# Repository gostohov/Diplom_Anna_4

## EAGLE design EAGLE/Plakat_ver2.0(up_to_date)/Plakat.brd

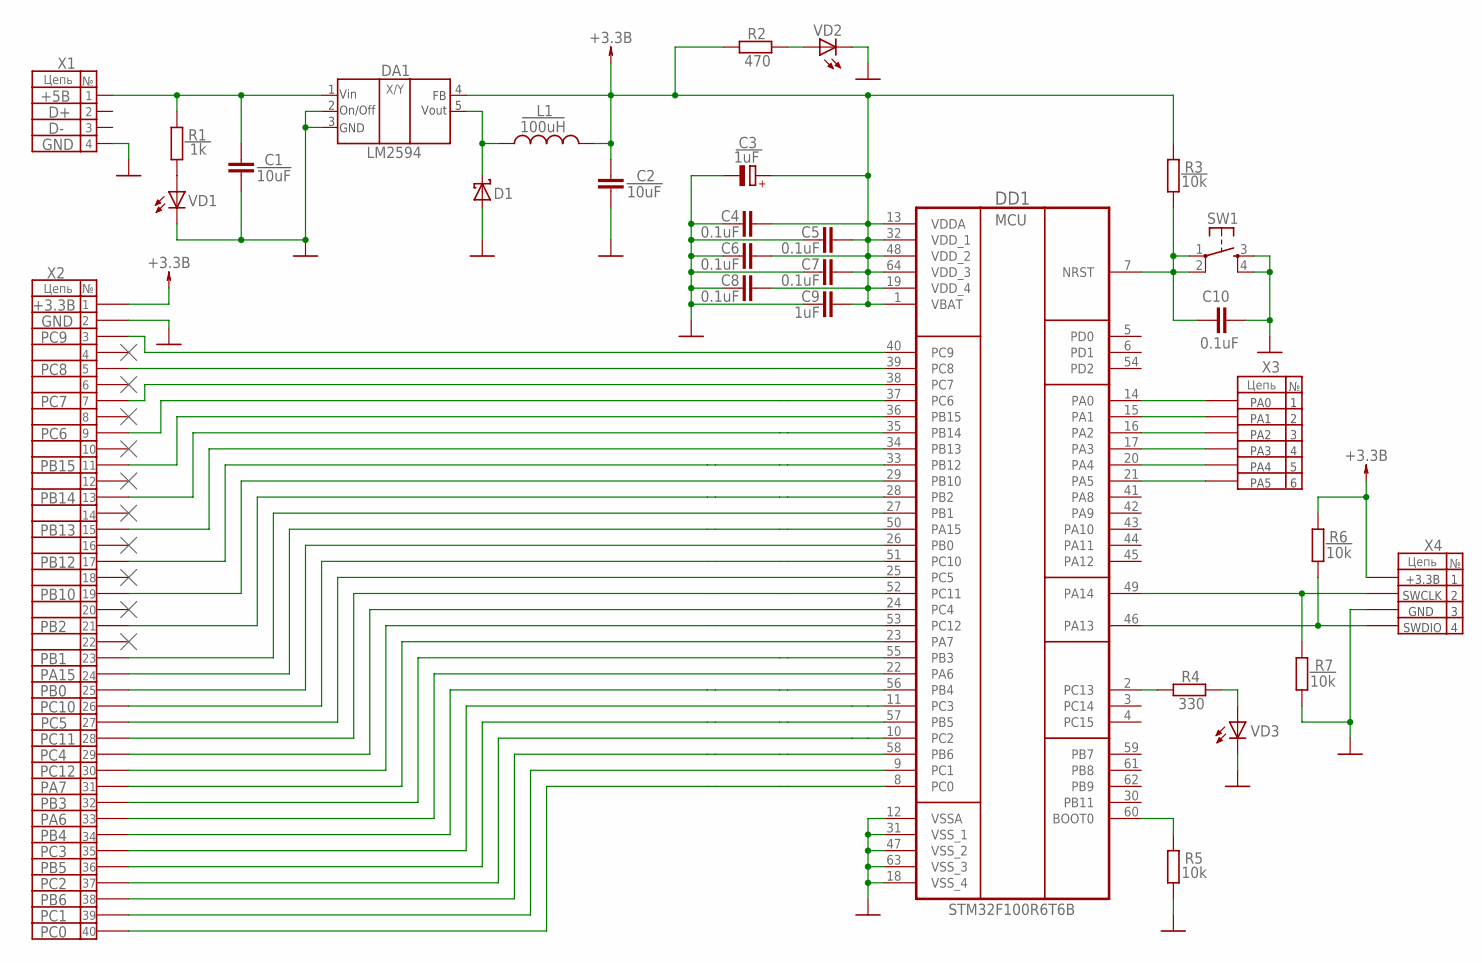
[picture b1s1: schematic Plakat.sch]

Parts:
C1, C2: 10uF; C0805
C3: 1uF; TYPE_A_TECAP
C4, C5, C6, C7, C8, C10: 0.1uF; C0805
C9: 1uF; C0805
D1: 1N5819-T; DO41-7.6
DA1: LM2594; LM2495
DD1: STM32F100R6T6B; QFP50P1200X1200X160-64N
L1: 100uH; 101KL
R1: 1k; R0805
R2: 470; R0805
R3, R5, R6, R7: 10k; R0805
R4: 330; R0805
SW1: DTSM-6
VD1, VD2, VD3: LED_E; LED_1206
X1: USB-MICROB
X2: PINHD-2X20; 2X20
X3: PINHD-1X6; 1X06
X4: PINHD-1X4; 1X04

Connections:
5V: C1.1, DA1.V(IN), R1.2, X1.VBUS
GND: C1.2, C2.2, C3.-, C4.1, C5.1, C6.1, C7.1, C8.1, C9.1, C10.2, D1.A, DA1.GND, DA1.ON/OFF, DD1.12 (VSSA), DD1.18 (VSS_4), DD1.31 (VSS_1), DD1.47 (VSS_2), DD1.63 (VSS_3), R5.1, R7.1, SW1.3, SW1.4, VD1.C, VD2.C, VD3.C, X1.GND, X1.MT1 (GND), X1.MT2 (GND), X2.2, X4.3
unnamed: DD1.60 (BOOT0), R5.2
unnamed: D1.C, DA1.OUT, L1.2
unnamed: DD1.14 (PA0), X3.1
unnamed: R1.1, VD1.A
unnamed: R4.2, VD3.A
unnamed: DD1.15 (PA1), X3.2
unnamed: DD1.2 (PC13), R4.1
unnamed: DD1.16 (PA2), X3.3
unnamed: DD1.17 (PA3), X3.4
unnamed: DD1.20 (PA4), X3.5
unnamed: DD1.21 (PA5), X3.6
unnamed: R2.2, VD2.A
unnamed: DD1.53 (PC12), X2.30
unnamed: C10.1, DD1.7 (NRST), R3.1, SW1.1, SW1.2
unnamed: DD1.40 (PC9), X2.3
unnamed: DD1.39 (PC8), X2.5
unnamed: DD1.38 (PC7), X2.7
unnamed: DD1.37 (PC6), X2.9
unnamed: DD1.36 (PB15), X2.11
unnamed: DD1.35 (PB14), X2.13
unnamed: DD1.34 (PB13), X2.15
unnamed: DD1.33 (PB12), X2.17
unnamed: DD1.29 (PB10), X2.19
unnamed: DD1.28 (PB2), X2.21
unnamed: DD1.27 (PB1), X2.23
unnamed: DD1.50 (PA15), X2.24
unnamed: DD1.26 (PB0), X2.25
unnamed: DD1.51 (PC10), X2.26
unnamed: DD1.25 (PC5), X2.27
unnamed: DD1.52 (PC11), X2.28
unnamed: DD1.24 (PC4), X2.29
unnamed: DD1.23 (PA7), X2.31
unnamed: DD1.55 (PB3), X2.32
unnamed: DD1.22 (PA6), X2.33
unnamed: DD1.56 (PB4), X2.34
unnamed: DD1.11 (PC3), X2.35
unnamed: DD1.57 (PB5), X2.36
unnamed: DD1.10 (PC2), X2.37
unnamed: DD1.58 (PB6), X2.38
unnamed: DD1.9 (PC1), X2.39
unnamed: DD1.8 (PC0), X2.40
SWCLK: DD1.49 (PA14), R7.2, X4.2
SWDIO: DD1.46 (PA13), R6.1, X4.4
VCC: C2.1, C3.+, C4.2, C5.2, C6.2, C7.2, C8.2, C9.2, DA1.FB, DD1.1 (VBAT), DD1.13 (VDDA), DD1.19 (VDD_4), DD1.32 (VDD_1), DD1.48 (VDD_2), DD1.64 (VDD_3), L1.1, R2.1, R3.2, R6.2, X2.1, X4.1

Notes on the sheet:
Цепь
+5B
GND
Vin
On/Off
Vout
+3.3В
SWDIO
SWCLK
PA0
PA1
PA2
PA3
PA4
PA5
MCU
PC9
PC8
PC7
PC6
PB15
PB14
PB13
PB12
PB10
PB2
PB1
PA15
PB0
PC10
PC5
PC11
PC4
PC12
PA7
PB3
PA6
PB4
PC3
PB5

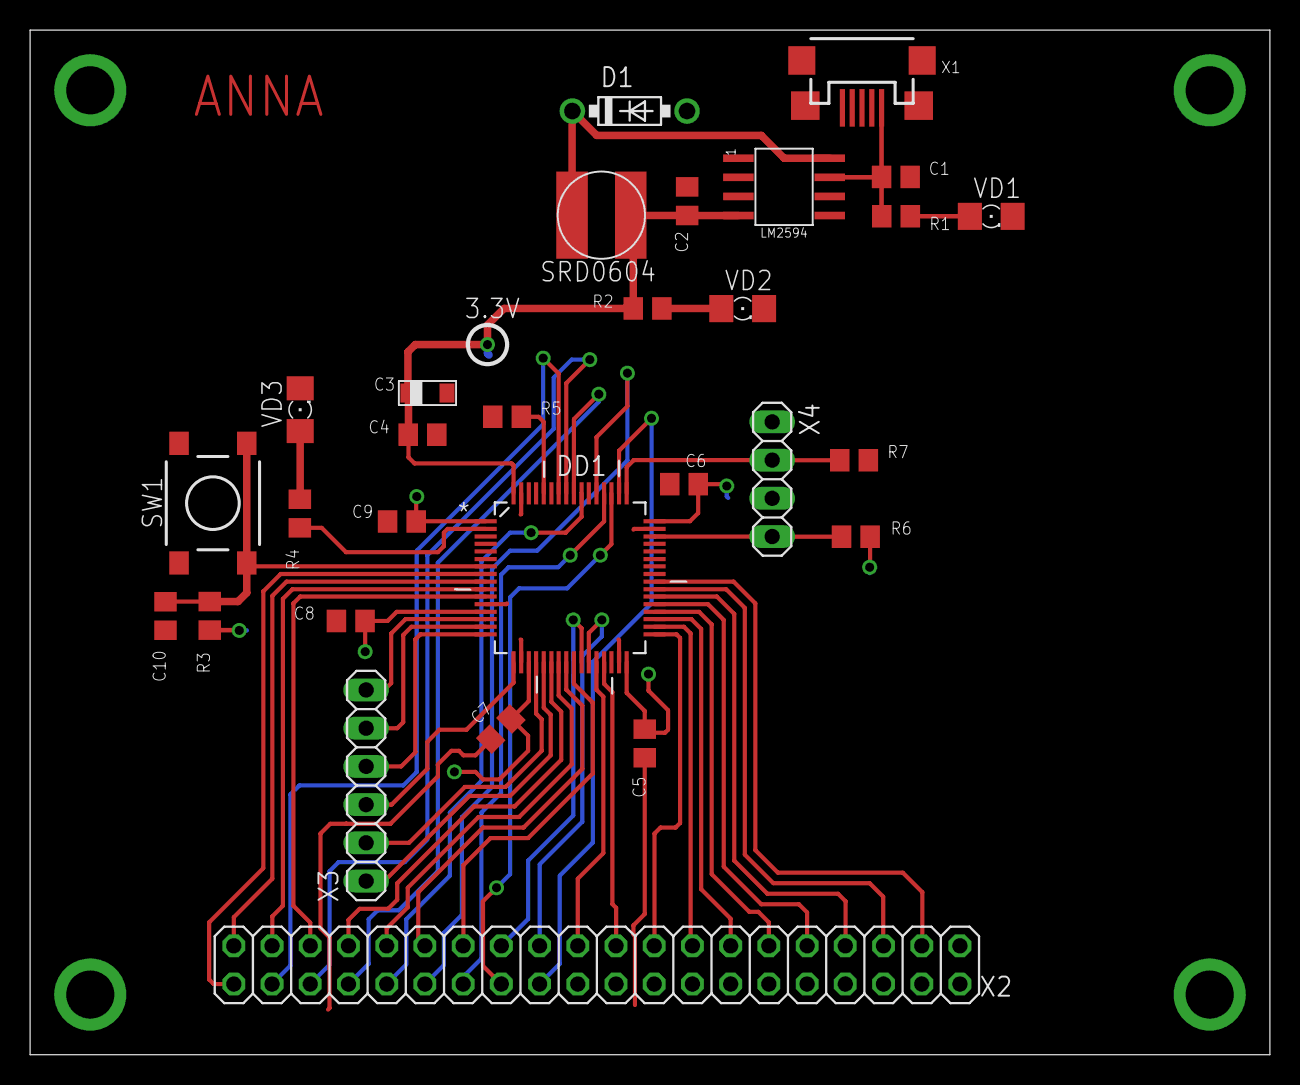
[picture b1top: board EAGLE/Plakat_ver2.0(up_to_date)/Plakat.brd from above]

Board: 2 copper layers, 82.4 x 68.1 mm, 29 parts (0 on the bottom side), 46 nets.

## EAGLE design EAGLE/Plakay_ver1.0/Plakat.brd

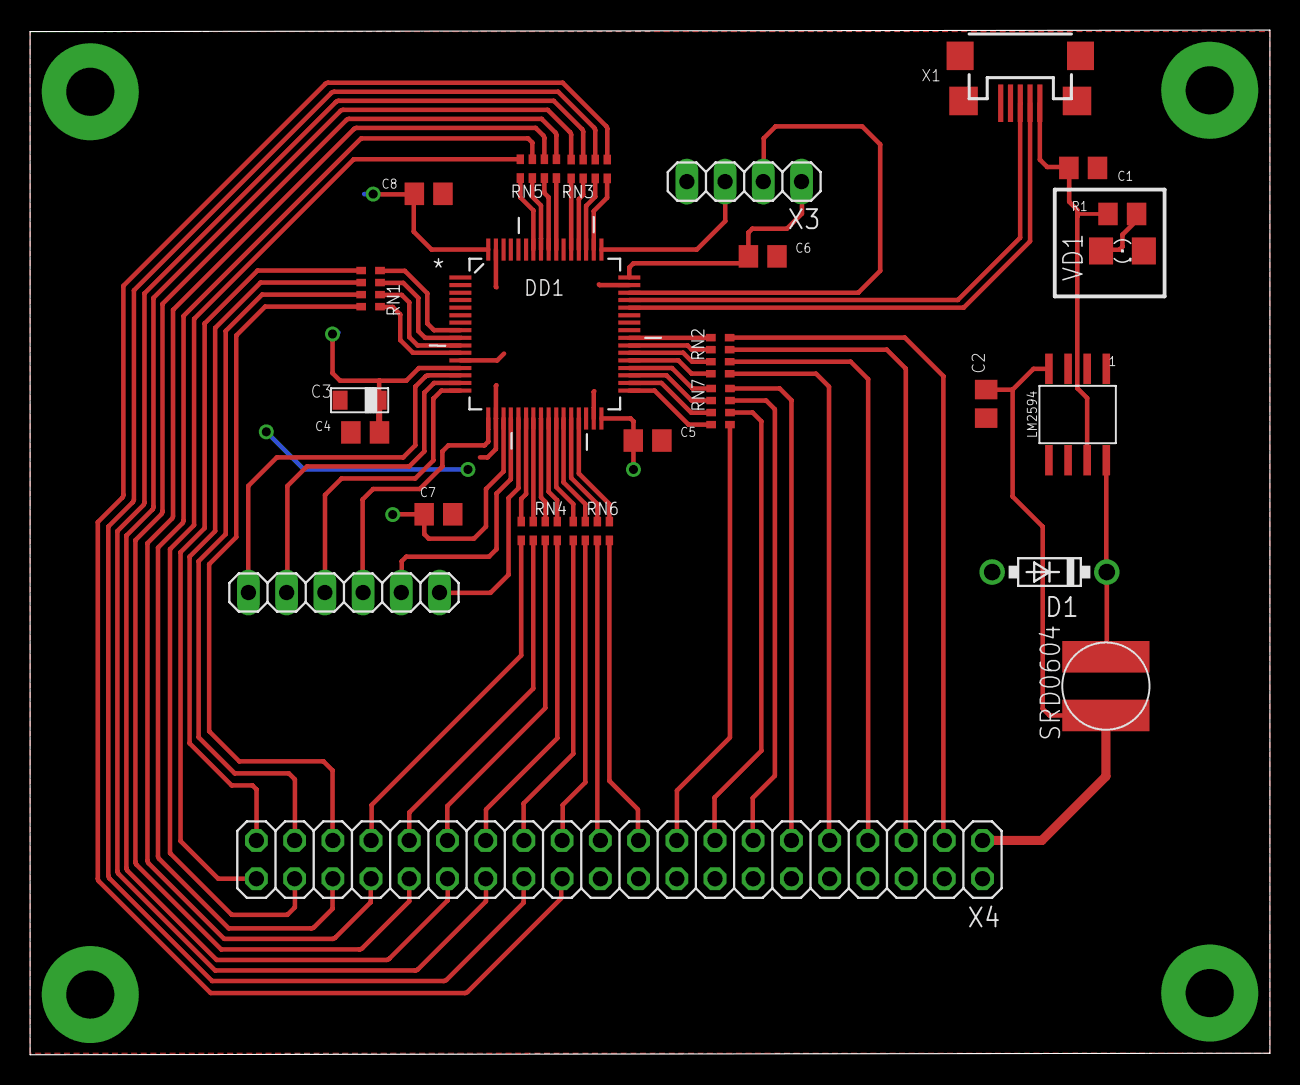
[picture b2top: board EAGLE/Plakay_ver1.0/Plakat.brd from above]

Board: 2 copper layers, 82.4 x 68.1 mm, 25 parts (0 on the bottom side), 71 nets.

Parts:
C1, C2: 10uF; C0805
C3: 1uF; TYPE_A_TECAP
C4, C5, C6, C7, C8: 100nF; C0805
D1: 1N5819-T; DO41-7.6
DA1: LM2594; LM2495
DD1: STM32F100R6T6B; QFP50P1200X1200X160-64N
L1: 100uH; 101KL
R1: 470; R0805
RN1, RN2, RN3, RN4, RN5, RN6, RN7: 100; 0603-ARC
VD1: LED_1206
X1: USB-MICROB
X2: 1X06
X3: 1X04
X4: 2X20

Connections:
DM: DD1.44, X1.D-
DP: DD1.45, X1.D+
GND: C1.2, C2.2, C3.-, C4.2, C5.2, C6.2, C7.2, C8.2, D1.A, DA1.GND, DA1.ON/OFF, DD1.12, DD1.18, DD1.31, DD1.47, DD1.63, VD1.C, X1.GND, X1.MT1, X1.MT2, X3.4, X4.2
unnamed: C1.1, DA1.V(IN), R1.2, X1.VBUS
unnamed: D1.C, DA1.OUT, L1.2
unnamed: DD1.14, X2.1
unnamed: R1.1, VD1.A
unnamed: DD1.8, RN1.4
unnamed: DD1.15, X2.2
unnamed: DD1.9, RN1.3
unnamed: DD1.16, X2.3
unnamed: DD1.17, X2.4
unnamed: DD1.20, X2.5
unnamed: DD1.21, X2.6
unnamed: DD1.10, RN1.2
unnamed: DD1.11, RN1.1
unnamed: DD1.24, RN4.2
unnamed: DD1.25, RN4.1
unnamed: DD1.37, RN2.4
unnamed: DD1.38, RN2.3
unnamed: DD1.39, RN2.2
unnamed: DD1.40, RN2.1
unnamed: DD1.51, RN3.3
unnamed: DD1.50, RN3.4
unnamed: DD1.22, RN4.4
unnamed: DD1.23, RN4.3
unnamed: DD1.26, RN6.4
unnamed: DD1.27, RN6.3
unnamed: DD1.55, RN5.4
unnamed: DD1.56, RN5.3
unnamed: DD1.57, RN5.2
unnamed: DD1.58, RN5.1
unnamed: DD1.28, RN6.2
unnamed: DD1.29, RN6.1
unnamed: DD1.33, RN7.4
unnamed: DD1.34, RN7.3
unnamed: DD1.35, RN7.2
unnamed: DD1.36, RN7.1
unnamed: RN2.8, X4.3
unnamed: RN2.7, X4.5
unnamed: RN2.6, X4.7
unnamed: RN2.5, X4.9
unnamed: RN7.8, X4.11
unnamed: RN7.7, X4.13
unnamed: RN7.6, X4.15
unnamed: RN7.5, X4.17
unnamed: RN6.8, X4.19
unnamed: RN6.7, X4.21
unnamed: RN6.6, X4.23
unnamed: RN6.5, X4.25
unnamed: RN4.8, X4.27
unnamed: RN4.7, X4.29
unnamed: RN4.6, X4.31
unnamed: RN4.5, X4.33
unnamed: RN1.8, X4.35
unnamed: RN1.7, X4.37
unnamed: RN1.6, X4.39
unnamed: RN1.5, X4.40
unnamed: RN5.8, X4.38
unnamed: RN5.7, X4.36
unnamed: RN5.6, X4.34
unnamed: RN5.5, X4.32
unnamed: RN3.8, X4.30
unnamed: RN3.7, X4.28
unnamed: RN3.6, X4.26
unnamed: DD1.52, RN3.2
unnamed: DD1.53, RN3.1
unnamed: RN3.5, X4.24
SWCLK: DD1.49, X3.3
SWDIO: DD1.46, X3.2
VCC: C2.1, C3.+, C4.1, C5.1, C6.1, C7.1, C8.1, DA1.FB, DD1.13, DD1.19, DD1.32, DD1.48, DD1.64, L1.1, X3.1, X4.1

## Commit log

2017-03-22 Nothing
2017-03-23 Добавила код и разводку, кнопок пока нет
2017-04-03 Создал папку docs
2017-04-07 Version 1.0
2017-04-11 version 1.1
2017-04-12 Glava 1. Version 1.0
    пока сделано только от 1.1 до 1.2.2
2017-04-12 Добавил чертежи
    Принципиальная схема - для сдачи Соловьеву. Она запушная, её надо
    переделывать, но для того, чтобы показать сойдет.
    Структурная схема - тоже для показа. Надо поправить основную надпись.
2017-04-12 Added Untitled Diagram.xml
2017-04-12 Create read emae me
2017-04-19 Add files via upload
    Написала полностью первую главу, готовый вариант.
2017-04-19 Add files via upload
    добавила содержание, интересно правильно ли шаблон выбран. Пока только первой главы
2017-04-28 Edited plakat_залипуха
2017-04-28 Plakat.sch was redrawed by the right way
2017-04-28 Modified Plakat.brd
2017-04-29 Created drawaings. Working with ИУ4 2205.05.01.00
2017-04-29 End: Сборочный чертеж и спецификацию
2017-04-29 Ended Печатная плата
2017-04-30 Modified Печатная плата.cdw
2017-05-02 Deleted 2 cdw
2017-05-15 Modified СБ, Э3, ПП
2017-05-18 Created analog pcb
2017-05-21 Created Plakat_ver2.0
    This version of PCB is up-to-date. Change list:
    1. Added RESET button
    2. Deleted resistor-arrays
    3. Modified SWD communication
    4. VBAT pull-up to VCC
    5. BOOT0 pulled-down throught resistor
2017-05-22 Created Цифровой модуль СП, СБ, ПП
2017-05-29 Я уже ничего не помню
2017-06-05 Кто инжинир? Я инжинир

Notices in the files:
parts and their libraries:
SparkFun-Connectors: Licensing: Creative Commons ShareAlike 4.0 International - https://creativecommons.org/licenses/by-sa/4.0
